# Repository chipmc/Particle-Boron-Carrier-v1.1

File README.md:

This carrier is to support the use of the Boron in outdoor environments.

Major functional goals for the project are:

Temp sensor in case I need to control LiPo charging
External watchdog timer - connect to either Enable or !RST
Single - button on / off so you can leave the battery and power plugged in
The ability for the device to power-cycle itself
ESD and fuse protection
Headers for i2c, SPI and IO
Big capacitor on DC-IN to support Solar Powered use case
External Real Time Clock as the Gen 3 devices lack this functionality.

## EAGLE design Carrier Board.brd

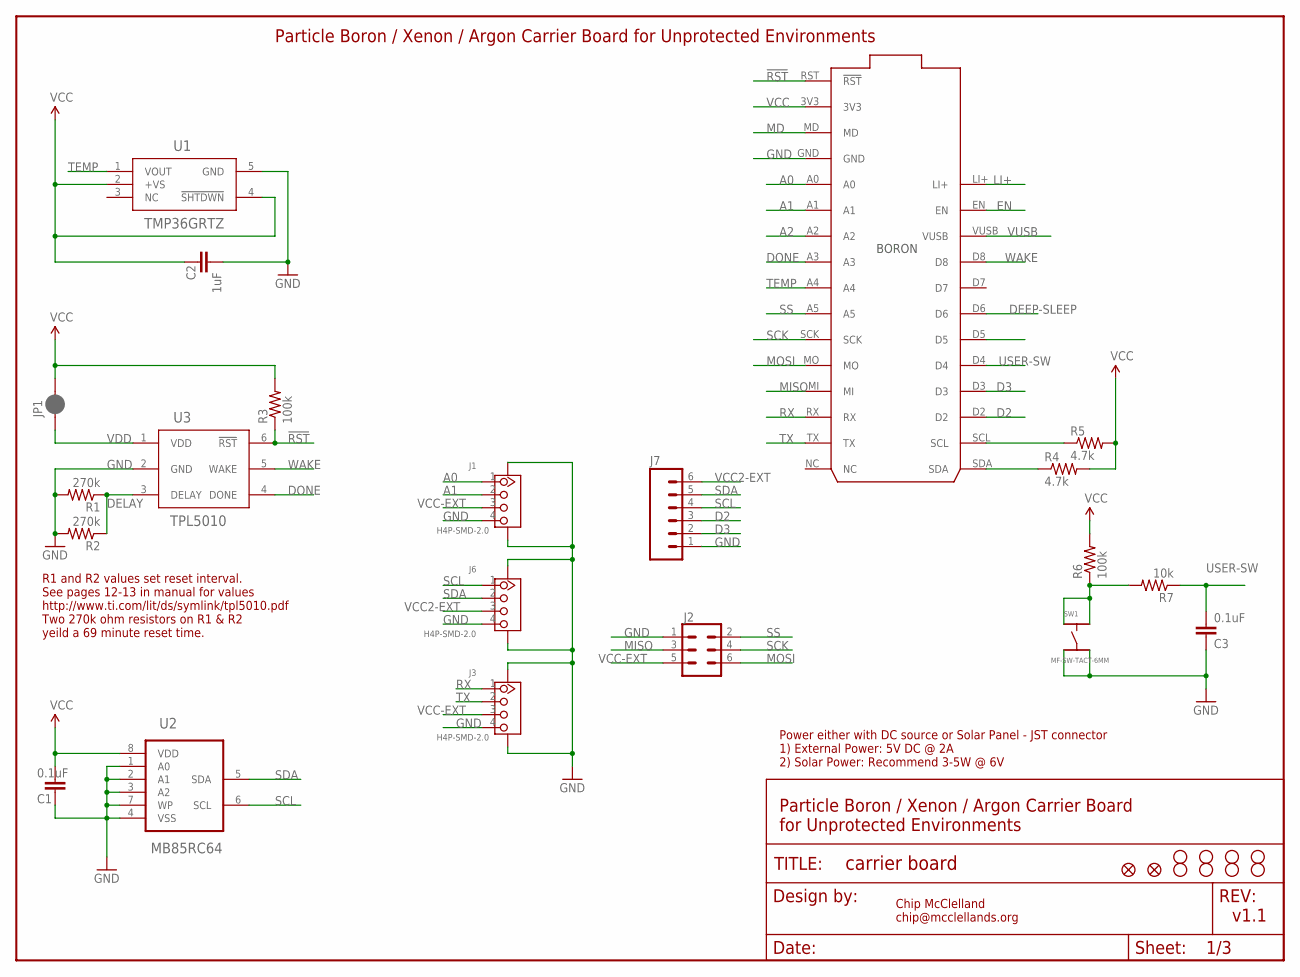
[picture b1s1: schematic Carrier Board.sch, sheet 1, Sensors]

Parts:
C1, C3: 0.1uF; 0805@1; MPN MF-CAP-0805-0.1uF
C2: 1uF; 0805@1; MPN MF-CAP-0805-1uF
FD1, FD2: FIDUCIALUFIDUCIAL; FIDUCIAL-MICRO
FRAME1: FRAME-LETTER; CREATIVE_COMMONS
H1, H2, H3, H4: STAND-OFF-M2.5
J1, J3, J6: H4P-SMD-2.0; HW4-SMD-2.0; MPN B4B-PH-SM4-TB(LF)(SN)
J2: CONN_03X22X3_SILK_MALE_PTH; 2X3
J7: M06LOCK; 1X06_LOCK
JP1: JUMPER-SMT_2_NC_PASTE_SILK; SMT-JUMPER_2_NC_PASTE_SILK
JP3, JP4, JP5, JP6: STAND-OFF
P1: PARTICLE-DEVICES-BORON; PARTICLE-DEVICES_BORON
R1, R2: 270k; 0805; MPN ERJ-P06F2703V
R3, R6: 100k; 0805; MPN MF-RES-0805-100K
R4, R5: 4.7k; 0805; MPN MF-RES-0805-4.7K
R7: 10k; 0805; MPN MF-RES-0805-10K
SW1: MF-SW-TACT-6MM; TACT6MM
U1: TMP36GRTZ; RJ_5; MANUFACTURER_PART_NUMBER TMP36GRTZ-REEL7
U2: MB85RC64; SOIC127P600X175-8N; MPN MB85RC64PNF-G-JNE1
U3: TPL5010; TSOT-23; MPN TPL5010DDCR

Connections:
!RST: P1.RST (!RST), R3.1, U3.6 (!RST)
A0: J1.1, P1.A0
A1: J1.2, P1.A1
A2: P1.A2
D2: J7.3, P1.D2; also elsewhere on the board
D3: J7.2, P1.D3; also elsewhere on the board
DEEP-SLEEP: P1.D6; also elsewhere on the board
DELAY: R1.1, R2.1, U3.3 (DELAY)
DONE: P1.A3, U3.4 (DONE)
EN: P1.EN; also elsewhere on the board
GND: C1.2, C2.2, C3.2, J1.4, J1.SS1, J1.SS2, J2.1, J3.4, J3.SS1, J3.SS2, J6.4, J6.SS1, J6.SS2, J7.1, P1.GND, R1.2, R2.2, SW1.P$3, SW1.P$4, U1.5 (GND), U2.1 (A0), U2.2 (A1), U2.3 (A2), U2.4 (VSS), U2.7 (WP), U3.2 (GND); also elsewhere on the board
LI+: P1.LI+; also elsewhere on the board
MD: P1.MD
MISO: J2.3, P1.MI
MOSI: J2.6, P1.MO
unnamed: R6.1, R7.2, SW1.P$1, SW1.P$2
RX: J3.1, P1.RX
SCK: J2.4, P1.SCK
SCL: J6.1, J7.4, P1.SCL, R5.1, U2.6 (SCL); also elsewhere on the board
SDA: J6.2, J7.5, P1.SDA, R4.1, U2.5 (SDA); also elsewhere on the board
SS: J2.2, P1.A5
TEMP: P1.A4, U1.1 (VOUT)
TX: J3.2, P1.TX
USER-SW: C3.1, P1.D4, R7.1
VCC: C1.1, C2.1, JP1.2, P1.3V3, R3.2, R4.2, R5.2, R6.2, U1.2 (+VS), U1.4 (!SHTDWN), U2.8 (VDD); also elsewhere on the board
VCC2-EXT: J6.3, J7.6; also elsewhere on the board
VCC-EXT: J1.3, J2.5, J3.3; also elsewhere on the board
VDD: JP1.1, U3.1 (VDD)
VUSB: P1.VUSB; also elsewhere on the board
WAKE: P1.D8, U3.5 (WAKE)

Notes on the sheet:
Chip McClelland chip@mcclellands.org
v1.1
Power either with DC source or Solar Panel - JST connector 1) External Power: 5V DC @ 2A 2) Solar Power: Recommend 3-5W @ 6V
Particle Boron / Xenon / Argon Carrier Board for Unprotected Environments
R1 and R2 values set reset interval. See pages 12-13 in manual for values http://www.ti.com/lit/ds/symlink/tpl5010.pdf Two 270k ohm resistors on R1 & R2 yeild a 69 minute reset time.
Particle Boron / Xenon / Argon Carrier Board for Unprotected Environments

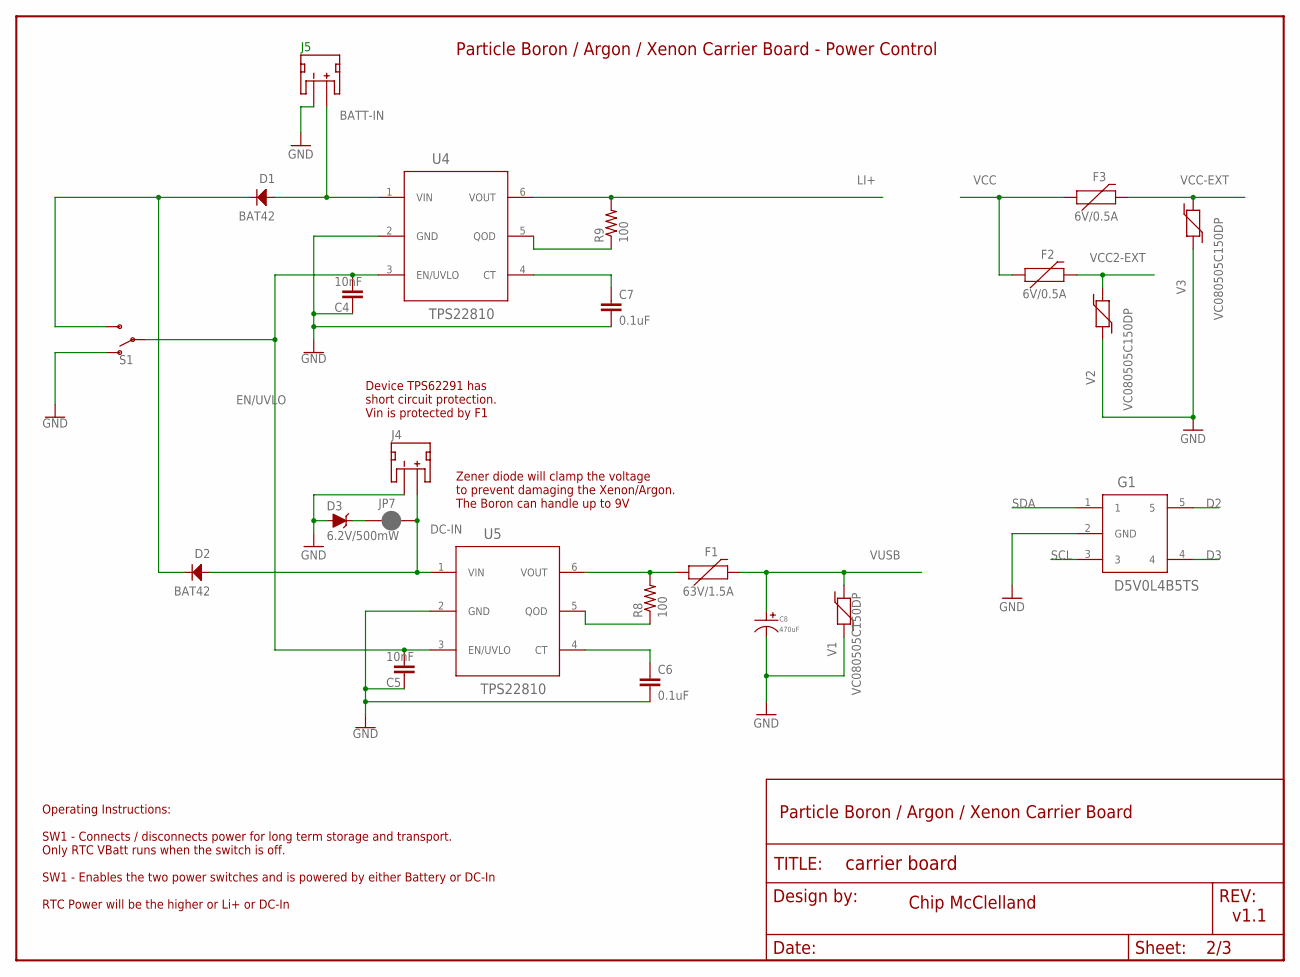
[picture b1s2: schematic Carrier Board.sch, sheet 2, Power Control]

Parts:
C4, C5: 10nF; 0805@1; MPN 08051C103K4T2A
C6, C7: 0.1uF; 0805@1; MPN MF-CAP-0805-0.1uF
C8: 470uF; CP10MM; MPN MF-CAP-10MM-470uF
D1, D2: BAT42; SOD-123
D3: 6.2V/500mW; PANASONIC_SMINI2-F5-B; MPN TDZ6V2J,115
F1: 63V/1.5A; 1206; MPN 046801.5NR
F2, F3: 6V/0.5A; 1206; MPN 0466.500NR
FRAME2: FRAME-LETTER; CREATIVE_COMMONS
G1: D5V0L4B5TS; SOT-23-5; MPN D5V0L4B5TS-7
J4, J5: S2B-PH-SM4-TB(LF)(SN); JST-2-SMD
JP7: JUMPER-SMT_2_NC_PASTE_SILK; SMT-JUMPER_2_NC_PASTE_SILK
R8, R9: 100; 0805; MPN MF-RES-0805-100
S1: SWITCH-SPDT-SMD-AYZ0202; SWITCH_DPDT_SMD_AYZ0202; MPN AYZ0202AGRLC
U4, U5: TPS22810; SOT-23-6; MPN TPS22810DBVT
V1, V2, V3: VC080505C150DP; 0805; MPN VC080505C150DP

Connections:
BATT-IN: D1.ANODE, J5.2 (+), U4.1 (VIN); also elsewhere on the board
D2: G1.5; also elsewhere on the board
D3: G1.4; also elsewhere on the board
DC-IN: D2.ANODE, J4.2 (+), JP7.1, U5.1 (VIN)
EN/UVLO: C4.1, C5.1, S1.2, U4.3 (EN/UVLO), U5.3 (EN/UVLO)
GND: C4.2, C5.2, C6.2, C7.2, C8.P$2, D3.A, G1.2 (GND), J4.1 (-), J5.1 (-), S1.1 (O), U4.2 (GND), U5.2 (GND), V1.1, V2.1, V3.1; also elsewhere on the board
LI+: R9.2, U4.6 (VOUT); also elsewhere on the board
unnamed: D3.C, JP7.2
unnamed: C6.1, U5.4 (CT)
unnamed: R8.1, U5.5 (QOD)
unnamed: F1.1, R8.2, U5.6 (VOUT)
unnamed: D1.CATHODE, D2.CATHODE, S1.3 (S)
unnamed: C7.1, U4.4 (CT)
unnamed: R9.1, U4.5 (QOD)
SCL: G1.3; also elsewhere on the board
SDA: G1.1; also elsewhere on the board
VCC: F2.1, F3.1; also elsewhere on the board
VCC2-EXT: F2.2, V2.2; also elsewhere on the board
VCC-EXT: F3.2, V3.2; also elsewhere on the board
VUSB: C8.P$1, F1.2, V1.2; also elsewhere on the board

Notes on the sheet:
Particle Boron / Argon / Xenon Carrier Board - Power Control
Chip McClelland
v1.1
Device TPS62291 has short circuit protection. Vin is protected by F1
Particle Boron / Argon / Xenon Carrier Board
Operating Instructions: SW1 - Connects / disconnects power for long term storage and transport. Only RTC VBatt runs when the switch is off. SW1 - Enables the two power switches and is powered by either Battery or DC-In RTC Power will be the higher or Li+ or DC-In
Zener diode will clamp the voltage to prevent damaging the Xenon/Argon. The Boron can handle up to 9V

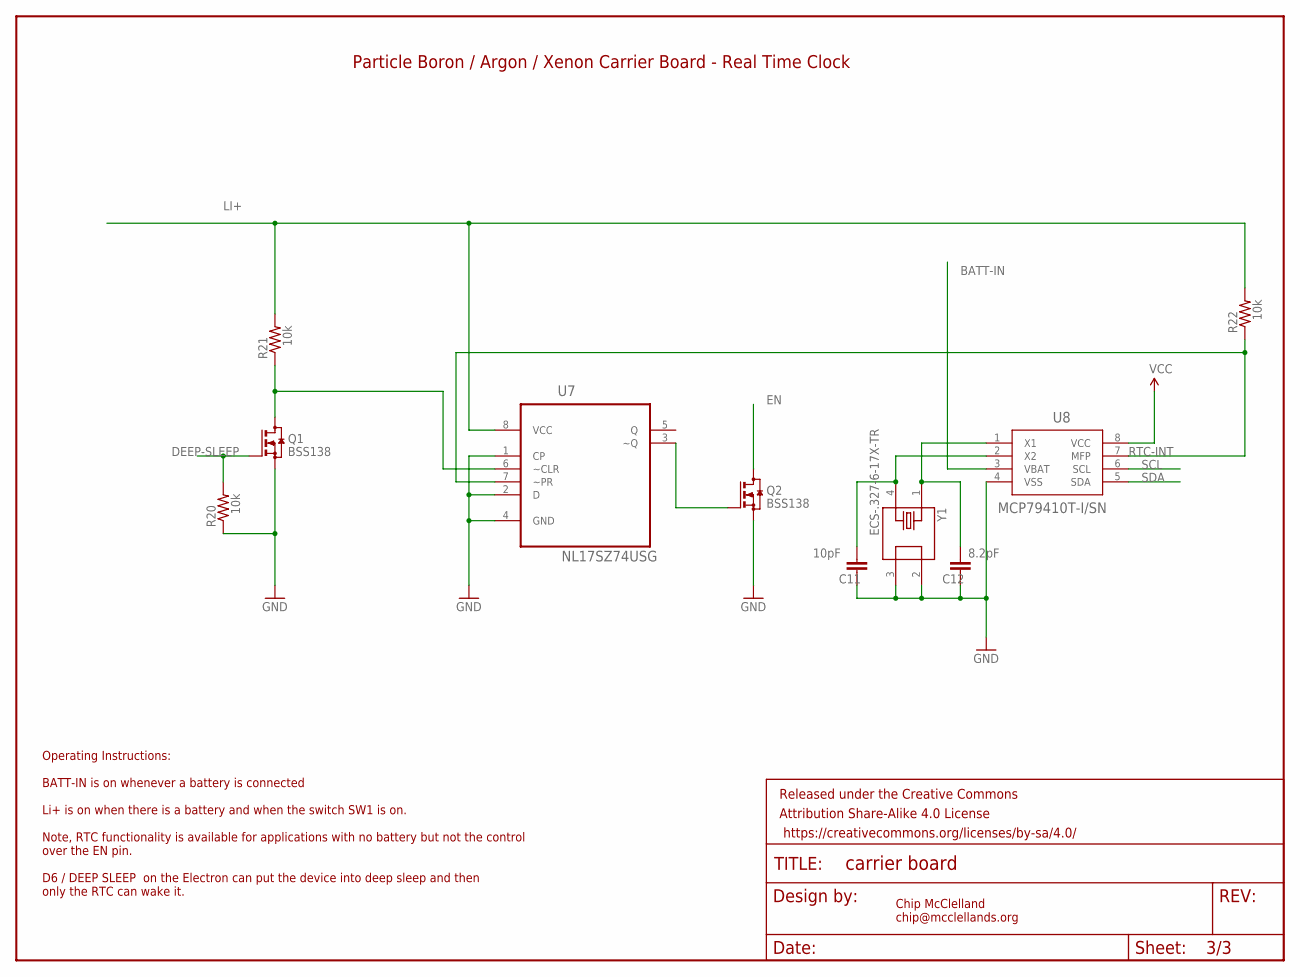
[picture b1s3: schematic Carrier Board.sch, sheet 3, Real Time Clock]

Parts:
C11: 10pF; 0805@1; MPN C0805C100JDGACTU‎
C12: 8.2pF; 0805@1; MPN C0805C829D5GACTU‎
FRAME3: FRAME-LETTER; CREATIVE_COMMONS
Q1, Q2: BSS138; SOT23; MPN MF-DSC-SOT233-BSS138
R20, R21, R22: 10k; 0805; MPN MF-RES-0805-10K
U7: NL17SZ74USG; SOP50P310X90-8N
U8: MCP79410T-I/SN; SOIC8-N_MC
Y1: ECS-.327-6-17X-TR; XTAL_ECS-.327-6-17X-TR

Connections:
BATT-IN: U8.3 (VBAT); also elsewhere on the board
DEEP-SLEEP: Q1.1 (G), R20.2; also elsewhere on the board
EN: Q2.3 (D); also elsewhere on the board
GND: C11.2, C12.2, Q1.2 (S), Q2.2 (S), R20.1, U7.1 (CP), U7.2 (D), U7.4 (GND), U8.4 (VSS), Y1.2, Y1.3; also elsewhere on the board
LI+: R21.2, R22.2, U7.8 (VCC); also elsewhere on the board
unnamed: Q2.1 (G), U7.3 (~Q)
unnamed: Q1.3 (D), R21.1, U7.6 (~CLR)
unnamed: C12.1, U8.1 (X1), Y1.1
unnamed: C11.1, U8.2 (X2), Y1.4
RTC-INT: R22.1, U7.7 (~PR), U8.7 (MFP)
SCL: U8.6 (SCL); also elsewhere on the board
SDA: U8.5 (SDA); also elsewhere on the board
VCC: U8.8 (VCC); also elsewhere on the board

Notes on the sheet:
Operating Instructions: BATT-IN is on whenever a battery is connected Li+ is on when there is a battery and when the switch SW1 is on. Note, RTC functionality is available for applications with no battery but not the control over the EN pin. D6 / DEEP SLEEP on the Electron can put the device into d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
Particle Boron / Argon / Xenon Carrier Board - Real Time Clock
Chip McClelland chip@mcclellands.org

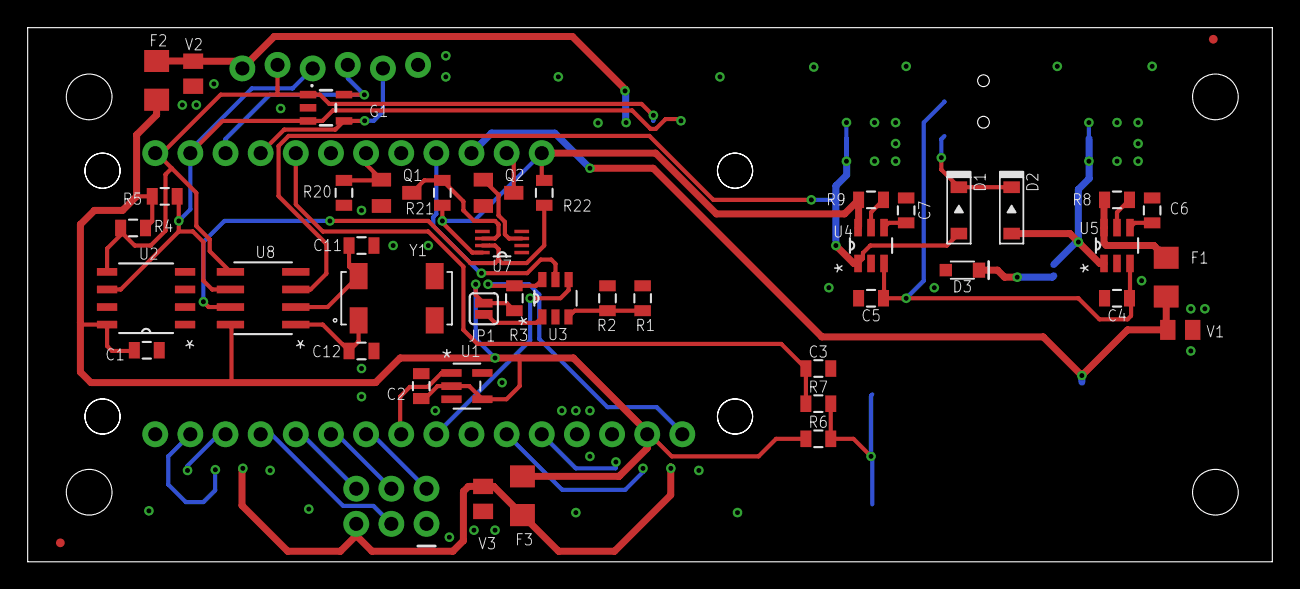
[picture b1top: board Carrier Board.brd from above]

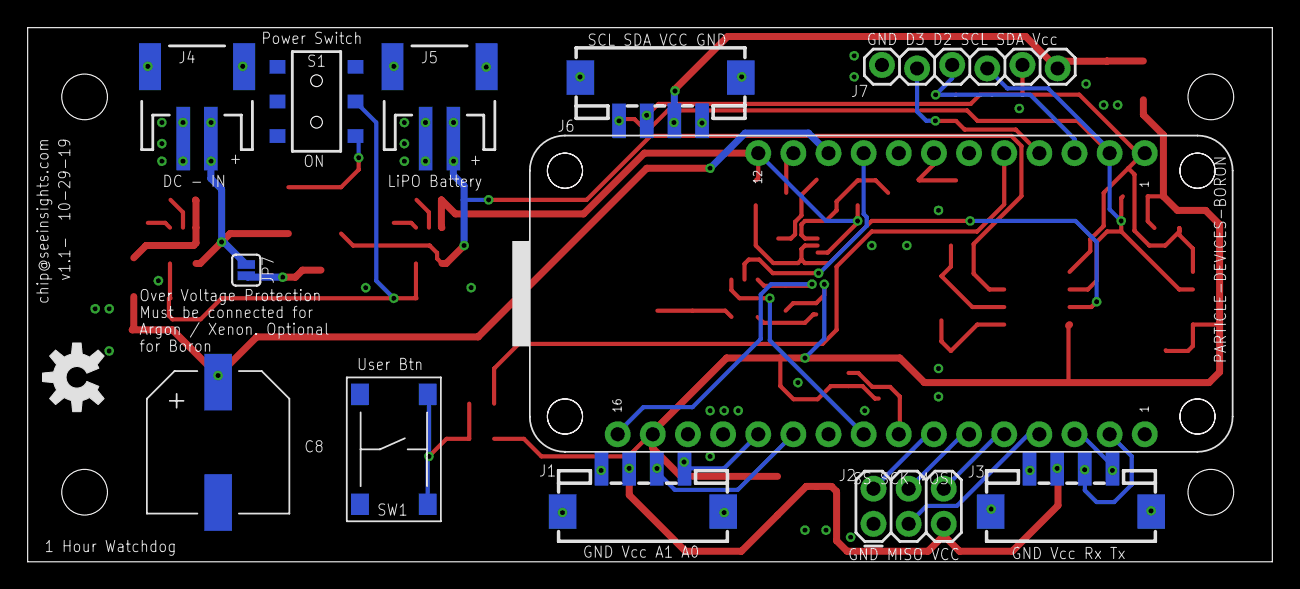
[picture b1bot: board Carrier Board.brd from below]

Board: 2 copper layers, 90.0 x 38.6 mm, 68 parts (13 on the bottom side), 43 nets.

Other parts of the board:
U$2: OSHW-LOGO-M

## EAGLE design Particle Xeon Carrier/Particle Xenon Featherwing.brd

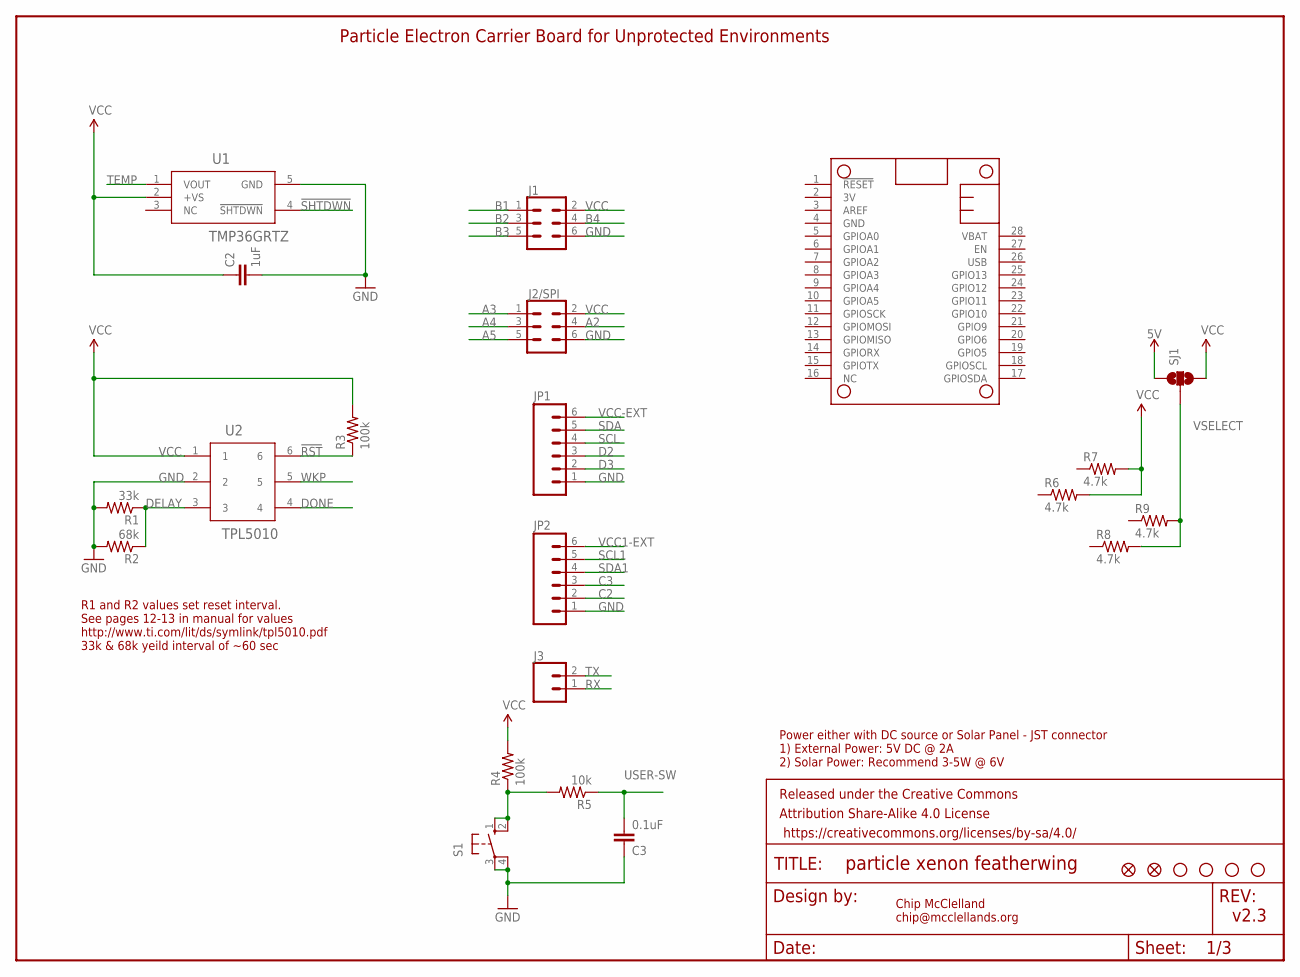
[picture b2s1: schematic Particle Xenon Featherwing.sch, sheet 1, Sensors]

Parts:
C2: 1uF; 0805@1
C3: 0.1uF; 0805@1
FD1, FD2: FIDUCIALUFIDUCIAL; FIDUCIAL-MICRO
FRAME1: FRAME-LETTER; CREATIVE_COMMONS
J1, J2/SPI: CONN_03X22X3_SILK_MALE_PTH; 2X3
J3: CONN_02; 1X02
JP1, JP2: M06LOCK; 1X06_LOCK
JP3, JP4, JP5, JP6: STAND-OFF
MS2: FEATHERWING_NODIM; FEATHERWING_DIM
R1: 33k; 0805
R2: 68k; 0805
R3, R4: 100k; 0805
R5: 10k; 0805
R6, R7, R8, R9: 4.7k; 0805
S1: 10-XX; B3F-10XX
SJ1: SOLDERJUMPER_2WAYPASTE1&2; SJ_3_PASTE1&2
U1: TMP36GRTZ; RJ_5
U2: TPL5010; TSOT-23

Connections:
5V: SJ1.1
!RST: R3.1, U2.6
!SHTDWN: U1.4 (!SHTDWN)
A2: J2/SPI.4
A3: J2/SPI.1
A4: J2/SPI.3
A5: J2/SPI.5
B1: J1.1
B2: J1.3
B3: J1.5
B4: J1.4
C2: JP2.2; also elsewhere on the board
C3: JP2.3; also elsewhere on the board
D2: JP1.3; also elsewhere on the board
D3: JP1.2; also elsewhere on the board
DELAY: R1.1, R2.1, U2.3
DONE: U2.4
GND: C2.2, C3.2, J1.6, J2/SPI.6, JP1.1, JP2.1, MS2.4 (GND), R1.2, R2.2, S1.3, S1.4 (P1), U1.5 (GND), U2.2; also elsewhere on the board
unnamed: R4.1, R5.2, S1.1 (S), S1.2 (S1)
RX: J3.1
SCL: JP1.4; also elsewhere on the board
SCL1: JP2.5; also elsewhere on the board
SDA: JP1.5; also elsewhere on the board
SDA1: JP2.4; also elsewhere on the board
TEMP: U1.1 (VOUT)
TX: J3.2
USER-SW: C3.1, R5.1
VCC: C2.1, J1.2, J2/SPI.2, R3.2, R4.2, R6.2, R7.2, SJ1.3, U1.2 (+VS), U2.1; also elsewhere on the board
VCC1-EXT: JP2.6; also elsewhere on the board
VCC-EXT: JP1.6; also elsewhere on the board
VSELECT: R8.2, R9.2, SJ1.2; also elsewhere on the board
WKP: U2.5

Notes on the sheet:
Chip McClelland chip@mcclellands.org
v2.3
Power either with DC source or Solar Panel - JST connector 1) External Power: 5V DC @ 2A 2) Solar Power: Recommend 3-5W @ 6V
Particle Electron Carrier Board for Unprotected Environments
R1 and R2 values set reset interval. See pages 12-13 in manual for values http://www.ti.com/lit/ds/symlink/tpl5010.pdf 33k & 68k yeild interval of ~60 sec

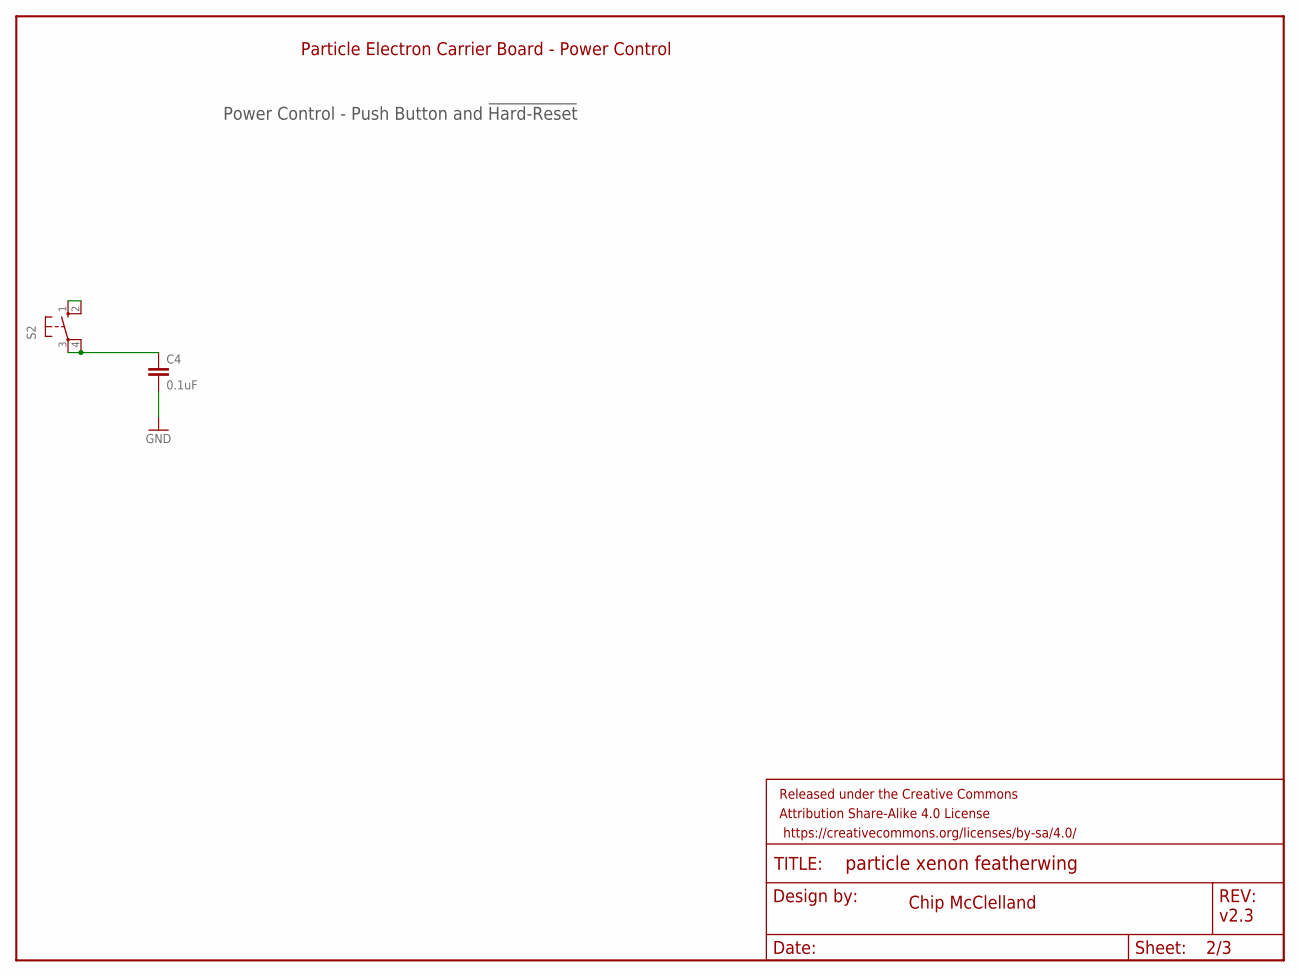
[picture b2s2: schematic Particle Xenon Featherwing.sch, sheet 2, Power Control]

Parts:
C4: 0.1uF; 0805@1
FRAME2: FRAME-LETTER; CREATIVE_COMMONS
S2: 40-XX-ROUND; B3F-40XX-ROUND

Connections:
GND: C4.2; also elsewhere on the board
unnamed: C4.1, S2.3, S2.4 (P1)
unnamed: S2.1 (S), S2.2 (S1)

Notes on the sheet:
Particle Electron Carrier Board - Power Control
Power Control - Push Button and !Hard-Reset
Chip McClelland
v2.3

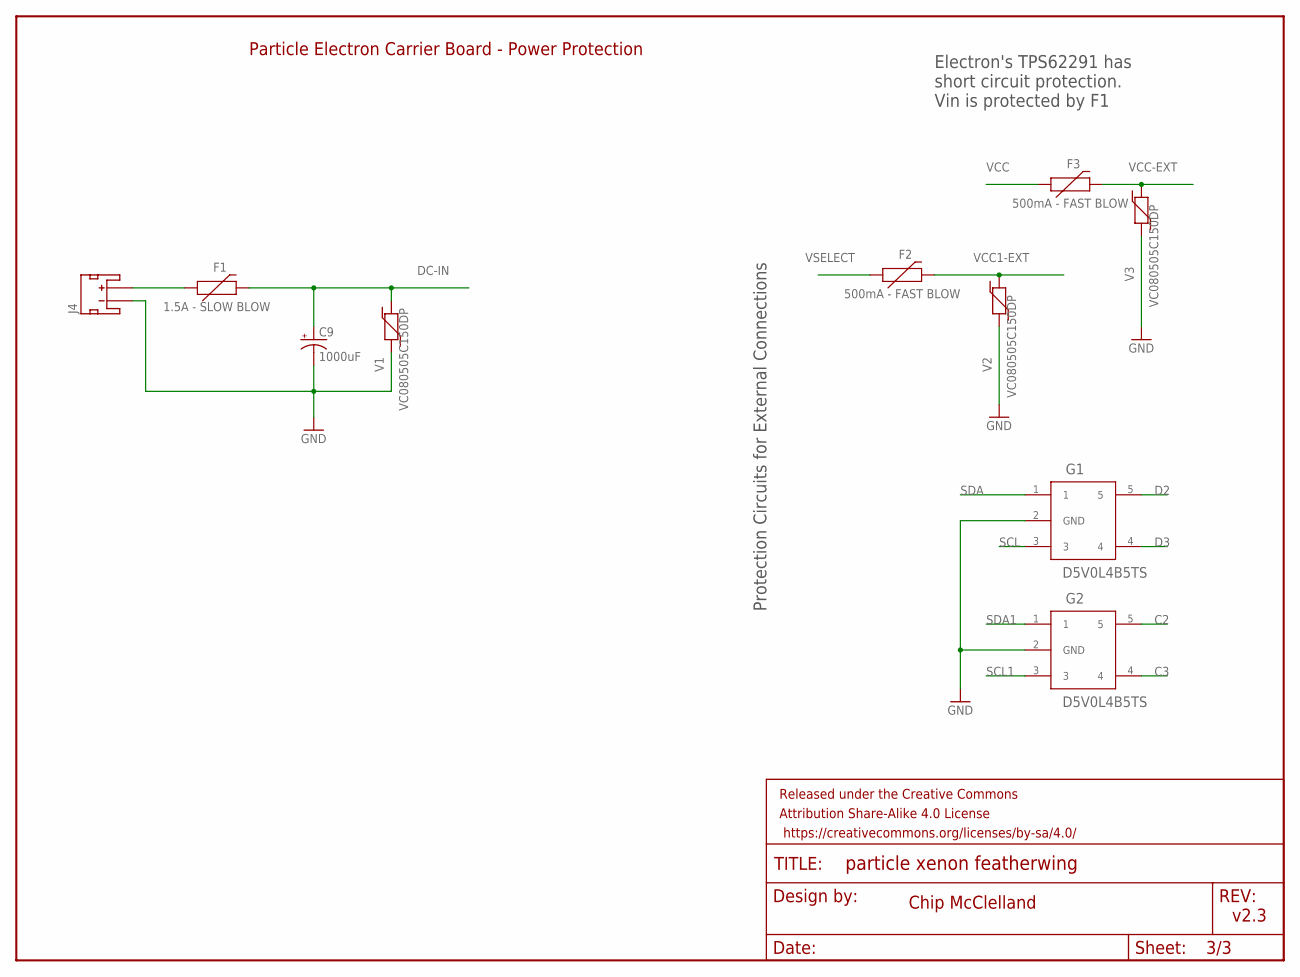
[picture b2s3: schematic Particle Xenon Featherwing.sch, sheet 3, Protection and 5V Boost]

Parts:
C9: 1000uF; PANASONIC_G
F1: 1.5A - SLOW BLOW; 1206
F2, F3: 500mA - FAST BLOW; 1206
FRAME3: FRAME-LETTER; CREATIVE_COMMONS
G1, G2: D5V0L4B5TS; SOT-23-5
J4: 5V @ 2A; JST-2-SMD
V1, V2, V3: VC080505C150DP; 0805

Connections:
C2: G2.5; also elsewhere on the board
C3: G2.4; also elsewhere on the board
D2: G1.5; also elsewhere on the board
D3: G1.4; also elsewhere on the board
DC-IN: C9.+, F1.2, V1.2
DC-IN-EXT: F1.1, J4.2 (+)
GND: C9.-, G1.2 (GND), G2.2 (GND), J4.1 (-), V1.1, V2.1, V3.1; also elsewhere on the board
SCL: G1.3; also elsewhere on the board
SCL1: G2.3; also elsewhere on the board
SDA: G1.1; also elsewhere on the board
SDA1: G2.1; also elsewhere on the board
VCC: F3.1; also elsewhere on the board
VCC1-EXT: F2.2, V2.2; also elsewhere on the board
VCC-EXT: F3.2, V3.2; also elsewhere on the board
VSELECT: F2.1; also elsewhere on the board

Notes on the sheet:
Protection Circuits for External Connections
Electron's TPS62291 has short circuit protection. Vin is protected by F1
Chip McClelland
v2.3
Particle Electron Carrier Board - Power Protection

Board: 2 copper layers, 43 parts (10 on the bottom side), 21 nets, no tracks yet.

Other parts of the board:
U$2: OSHW-LOGO-M

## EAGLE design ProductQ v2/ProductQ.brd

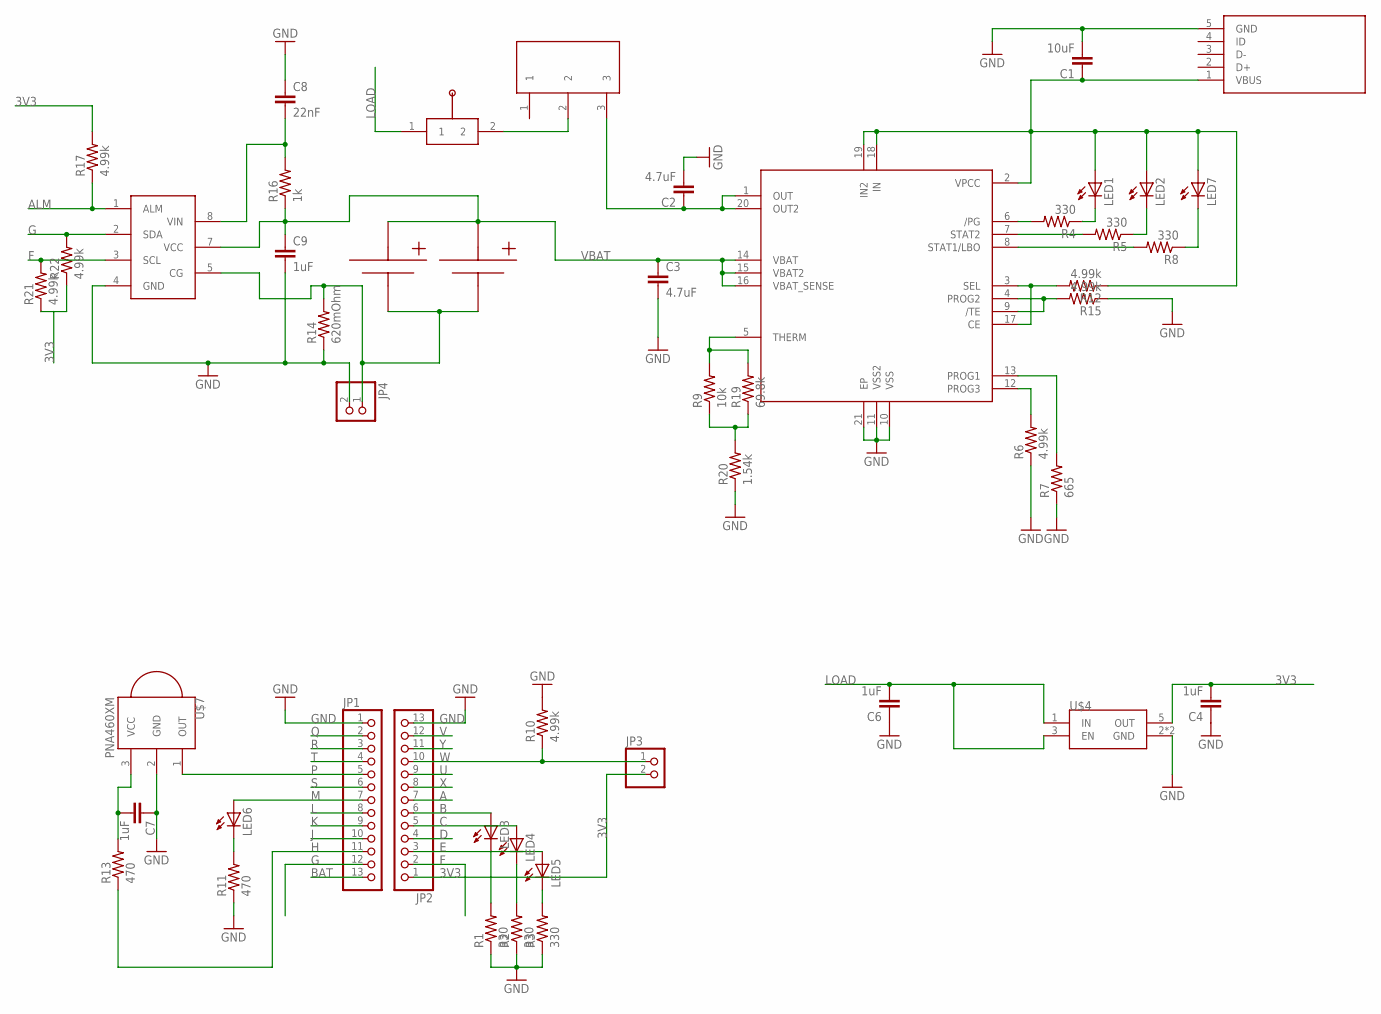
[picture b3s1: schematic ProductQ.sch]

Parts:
C1: 10uF; C0402
C2, C3: 4.7uF; C0402
C4, C6, C7, C9: 1uF; C0402
C8: 22nF; C0402
JP1, JP2: PINHD-1X13; 1X13
JP3: PINHD-1X2/90; 1X02/90
JP4: PINHD-1X2; 1X02
LED1, LED2, LED3, LED4, LED5, LED7: LEDCHIP-LED0805; CHIP-LED0805
LED6: LED3MM
R1, R2, R3, R4, R5, R8: 330; R0402
R6, R10, R12, R15, R17, R21, R22: 4.99k; R0402
R7: 665; R0402
R9: 10k; R0402
R11, R13: 470; R0402
R14: 620mOhm; R0603
R16: 1k; R0402
R19: 69.8k; R0402
R20: 1.54k; R0402
U$1: MCP73871; QFN_20
U$2: SPDT_THRU
U$3: USB_MINI
U$4: TPS782XX; SOT23-5L
U$5, U$6: 18650SMD; 18650KEYSTONE
U$7: PNA460XM
U$8: STC3105
U$9: MANUAL_SWITCH

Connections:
3V3: C4.2, JP2.1, JP3.2, R17.2, R21.1, R22.1, U$4.5 (OUT)
A: JP2.7
ALM: R17.1, U$8.1 (ALM)
B: JP2.6, LED3.A
BAT: JP1.13
C: JP2.5, LED4.A
D: JP2.4
E: JP2.3, LED5.A
F: JP2.2, R21.2, U$8.3 (SCL)
G: JP1.12, R22.2, U$8.2 (SDA)
GND: C1.2, C2.2, C3.2, C4.1, C6.1, C7.1, C8.1, C9.2, JP1.1, JP2.13, JP4.2, R1.1, R2.1, R3.1, R6.1, R7.1, R10.2, R11.1, R14.1, R15.1, R20.1, U$1.10 (VSS), U$1.11 (VSS2), U$1.21 (EP), U$3.5 (GND), U$4.2 (GND), U$4.4 (GND), U$7.2 (GND), U$8.4 (GND)
H: JP1.11, R13.1
J: JP1.10
K: JP1.9
L: JP1.8
LOAD: C6.2, U$4.1 (IN), U$4.3 (EN), U$9.1
M: JP1.7, LED6.A
unnamed: JP4.1, R14.2, U$5.P$2, U$6.P$2, U$8.5 (CG)
unnamed: R9.2, R19.2, U$1.5 (THERM)
unnamed: R7.2, U$1.13 (PROG1)
unnamed: R6.2, U$1.12 (PROG3)
unnamed: LED6.K (C), R11.2
unnamed: LED4.C, R2.2
unnamed: R4.2, U$1.6 (/PG)
unnamed: LED1.C, R4.1
unnamed: LED2.C, R5.1
unnamed: R5.2, U$1.7 (STAT2)
unnamed: R8.2, U$1.8 (STAT1/LBO)
unnamed: LED7.C, R8.1
unnamed: LED5.C, R3.2
unnamed: LED3.C, R1.2
unnamed: C8.2, R16.2, U$8.8 (VIN)
unnamed: C1.1, LED1.A, LED2.A, LED7.A, R12.1, U$1.2 (VPCC), U$1.18 (IN), U$1.19 (IN2), U$3.1 (VBUS)
unnamed: C7.2, R13.2, U$7.3 (VCC)
unnamed: R12.2, U$1.3 (SEL), U$1.17 (CE)
unnamed: R15.2, U$1.4 (PROG2), U$1.9 (/TE)
unnamed: U$2.2, U$9.2
unnamed: C2.1, U$1.1 (OUT), U$1.20 (OUT2), U$2.3
unnamed: R9.1, R19.1, R20.2
P: JP1.5, U$7.1 (OUT)
Q: JP1.2
R: JP1.3
S: JP1.6
T: JP1.4
U: JP2.9
V: JP2.12
VBAT: C3.1, C9.1, R16.1, U$1.14 (VBAT), U$1.15 (VBAT2), U$1.16 (VBAT_SENSE), U$5.P$1, U$6.P$1, U$8.7 (VCC)
W: JP2.10, JP3.1, R10.1
X: JP2.8
Y: JP2.11

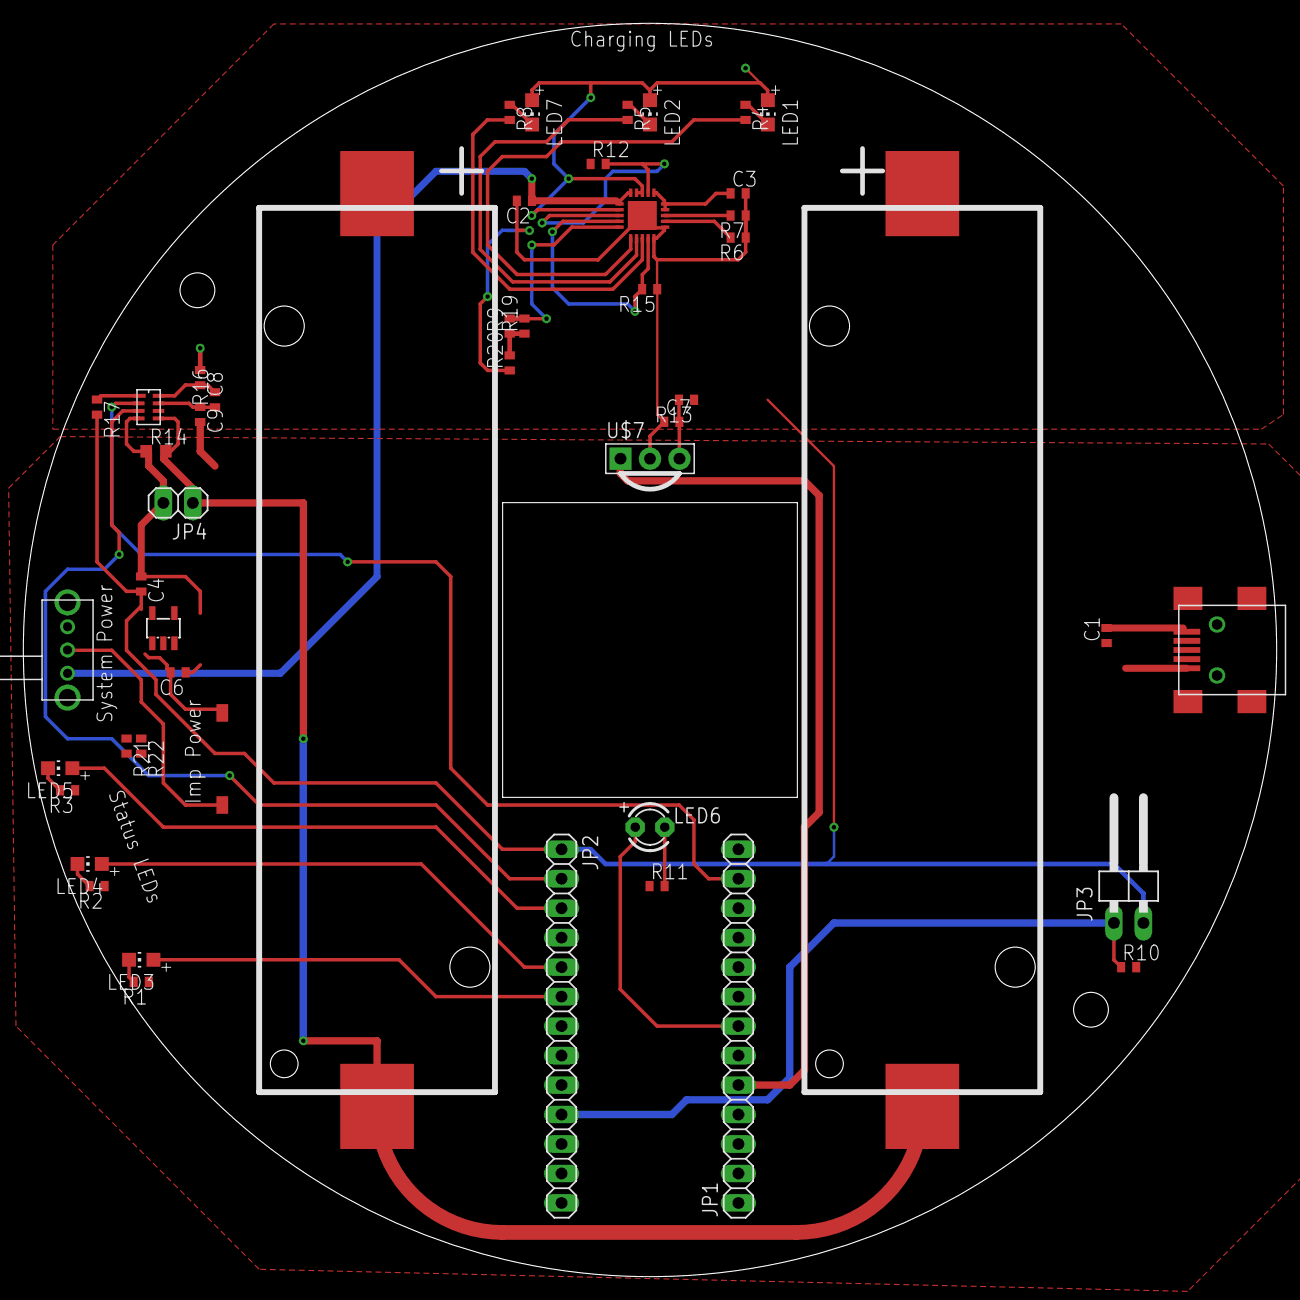
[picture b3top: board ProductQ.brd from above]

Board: 2 copper layers, 108.0 x 108.0 mm, 49 parts (0 on the bottom side), 36 nets.

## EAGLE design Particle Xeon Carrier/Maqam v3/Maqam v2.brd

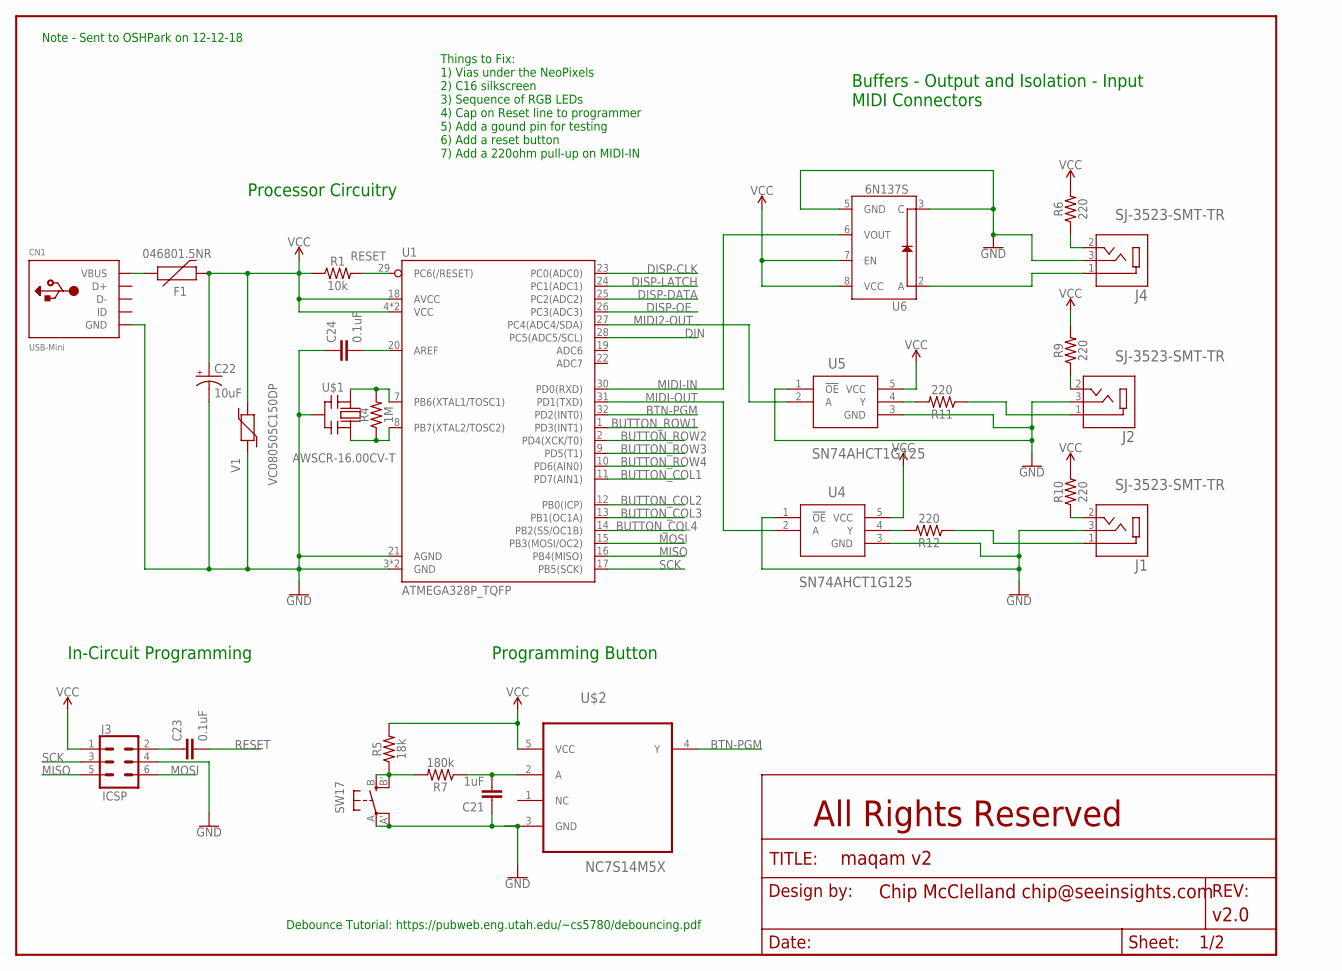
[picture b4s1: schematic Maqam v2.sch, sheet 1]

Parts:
C21: 1uF; 0805
C22: 10uF; EIA3216
C23, C24: 0.1uF; 0805
CN1: USB-Mini; USB-MINIB
F1: 046801.5NR; 1206
FRAME2: FRAME-LETTERNO_PACKAGE; DUMMY
J1, J2, J4: SJ-3523-SMT-TR; CUI_SJ-3523-SMT-TR
J3: ICSP; 2X3-SHROUDED
R1: 10k; 0805
R4: 1M; 0805
R5: 18k; 0805
R6, R9, R10, R11, R12: 220; 0805
R7: 180k; 0805
SW17: SPST_TACT-EVQQ2; EVQ-Q2
U1: ATMEGA328P_TQFP; TQFP32-08
U4, U5: SN74AHCT1G125; DBV5-L
U6: 6N137S; 8-SMD
U$1: AWSCR-16.00CV-T; AWSCR
U$2: NC7S14M5X; SOT-23-5
V1: VC080505C150DP; 0805

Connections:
BTN-PGM: U1.32 (PD2(INT0)), U$2.4 (Y)
BUTTON_COL1: U1.11 (PD7(AIN1)); also elsewhere on the board
BUTTON_COL2: U1.12 (PB0(ICP)); also elsewhere on the board
BUTTON_COL3: U1.13 (PB1(OC1A)); also elsewhere on the board
BUTTON_COL4: U1.14 (PB2(SS/OC1B)); also elsewhere on the board
BUTTON_ROW1: U1.1 (PD3(INT1)); also elsewhere on the board
BUTTON_ROW2: U1.2 (PD4(XCK/T0)); also elsewhere on the board
BUTTON_ROW3: U1.9 (PD5(T1)); also elsewhere on the board
BUTTON_ROW4: U1.10 (PD6(AIN0)); also elsewhere on the board
DIN: U1.28 (PC5(ADC5/SCL)); also elsewhere on the board
DISP-CLK: U1.23 (PC0(ADC0)); also elsewhere on the board
DISP-DATA: U1.25 (PC2(ADC2)); also elsewhere on the board
DISP-LATCH: U1.24 (PC1(ADC1)); also elsewhere on the board
DISP-OE: U1.26 (PC3(ADC3)); also elsewhere on the board
GND: C21.1, C22.-, C24.1, CN1.GND, J1.3, J2.3, J3.4, J4.3, SW17.A, SW17.A' (P1), U1.3 (GND), U1.5 (GND), U1.21 (AGND), U4.1 (!OE), U4.3 (GND), U5.1 (!OE), U5.3 (GND), U6.3 (C), U6.5 (GND), U$1.2 (GND), U$2.3 (GND), V1.1; also elsewhere on the board
MIDI2-OUT: U1.27 (PC4(ADC4/SDA)), U5.2 (A)
MIDI-IN: U1.30 (PD0(RXD)), U6.6 (VOUT)
MIDI-OUT: U1.31 (PD1(TXD)), U4.2 (A)
MISO: J3.5, U1.16 (PB4(MISO))
MOSI: J3.6, U1.15 (PB3(MOSI/OC2))
unnamed: C24.2, U1.20 (AREF)
unnamed: J1.1, R12.1
unnamed: R4.1, U1.8 (PB7(XTAL2/TOSC2)), U$1.3 (OUT)
unnamed: C23.1, J3.2
unnamed: R4.2, U1.7 (PB6(XTAL1/TOSC1)), U$1.1 (IN)
unnamed: J2.1, R11.1
unnamed: J4.2, R6.1
unnamed: J4.1, U6.2 (A)
unnamed: J1.2, R10.1
unnamed: J2.2, R9.1
unnamed: R12.2, U4.4 (Y)
unnamed: R11.2, U5.4 (Y)
unnamed: CN1.VBUS, F1.1
unnamed: R5.1, R7.2, SW17.B (S), SW17.B' (S1)
unnamed: C21.2, R7.1, U$2.2 (A)
RESET: C23.2, R1.2, U1.29 (PC6(/RESET))
SCK: J3.3, U1.17 (PB5(SCK))
VCC: C22.+, F1.2, J3.1, R1.1, R5.2, R6.2, R9.2, R10.2, U1.4 (VCC), U1.6 (VCC), U1.18 (AVCC), U4.5 (VCC), U5.5 (VCC), U6.7 (EN), U6.8 (VCC), U$2.5 (VCC), V1.2; also elsewhere on the board

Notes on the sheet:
Debounce Tutorial: https://pubweb.eng.utah.edu/~cs5780/debouncing.pdf
Processor Circuitry
Buffers - Output and Isolation - Input MIDI Connectors
In-Circuit Programming
Programming Button
All Rights Reserved
Note - Sent to OSHPark on 12-12-18
Things to Fix: 1) Vias under the NeoPixels 2) C16 silkscreen 3) Sequence of RGB LEDs 4) Cap on Reset line to programmer 5) Add a gound pin for testing 6) Add a reset button 7) Add a 220ohm pull-up on MIDI-IN

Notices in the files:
parts and their libraries:
SparkFun-Aesthetics: Licensing: Creative Commons ShareAlike 4.0 International - https://creativecommons.org/licenses/by-sa/4.0
SparkFun-Aesthetics: Released under the Creative Commons Attribution Share-Alike 4.0 License
SparkFun-Aesthetics: https://creativecommons.org/licenses/by-sa/4.0
